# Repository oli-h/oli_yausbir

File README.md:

# oli_yausbir
A LIRC-Plugin (i.e. driver) for "yaUsbIR V3 LIRC USB IR Empfänger/Sender/Einschalter"

Just google for "yaUsbIR V3" and you quickly find info about this little InfraRed-Receiver/Transmitter/PowerSwitch-device

## Notes
- Work in progress
- Logging not yet proper. It just prints to stdout.

## Build and usage
Ensure you installed libusb-1.0-0-dev and liblirc-dev (`sudo apt install...`)

Build with `./build.sh` (requires cmake).

Then use the well-known LIRC-Tools like this:
- `mode2 -U build/ -H oli_yausbir`
- `xmode2 -U build/ -H oli_yausbir`
- `irrecord -U build/ -H oli_yausbir`
- `lircd --nodaemon -U build -H oli_yausbir`
- etc...

Finally copy the compile/link-result `liboli_yausbir.so` to directory `/usr/lib/x86_64-linux-gnu/lirc/plugins/` (Cross-check with property `plugindir` in *your* `/etc/lirc/lirc_options.conf`). Then you don't need to specify `-U ...` any more.

To avoid setting the driver explicit with `-H oli_yausbir` you can also set it globally in `/etc/lirc/lirc_options.conf`:

```
[lircd]
...
driver = oli_yausbir
...
```

## Sending control-commands
The yaUsbIr-Board understands several control-commands. This PlugIn-driver here supports sending such control-commands (Note: Sending 'any' IR-Codes with a real IR-Trasmitter-LED - which must be attached to the yaUsbIr-Board - is *not* yet supported)

You need to copy [yaUsbIR_V3_lircd.conf](./yaUsbIr-Doc/yausbirv3.003/yaUsbIR_V3_lircd.conf) to `/etc/lirc/lircd.conf.d/` and (re)start `lircd` first *before* you can can anything with `irsend`.

Check if "sending control-commands" work by switching the red LED (on yaUsbIr-Board) on and off:
- `irsend SEND_ONCE yaUsbIR_control C_IR 8 0 C_END` turn *off*
- `irsend SEND_ONCE yaUsbIR_control C_IR 8 1 C_END` turn *on*

The most relevant command for you then probably is:
- `irsend SEND_ONCE yaUsbIR_control C_IR 1 1 0 C_END` to start learning the "Power-IR-Code"

See [Anleitung_yaUsbIR V3.4.pdf](./yaUsbir-Doc/Anleitung_yaUsbIR V3.4.pdf) for details and a list of all commands.

## udev
Write this into `/lib/udev/rules.d/99-yausbir.rules` to give normal user access to the USB-Device.
Other wise you have to start all tools (`xmode2`, `irrecord`, etc) as root.

```
SUBSYSTEM=="usb", ATTRS{idVendor}=="10c4", ATTRS{idProduct}=="876c", MODE="0666"
```
Simply reboot to take effect

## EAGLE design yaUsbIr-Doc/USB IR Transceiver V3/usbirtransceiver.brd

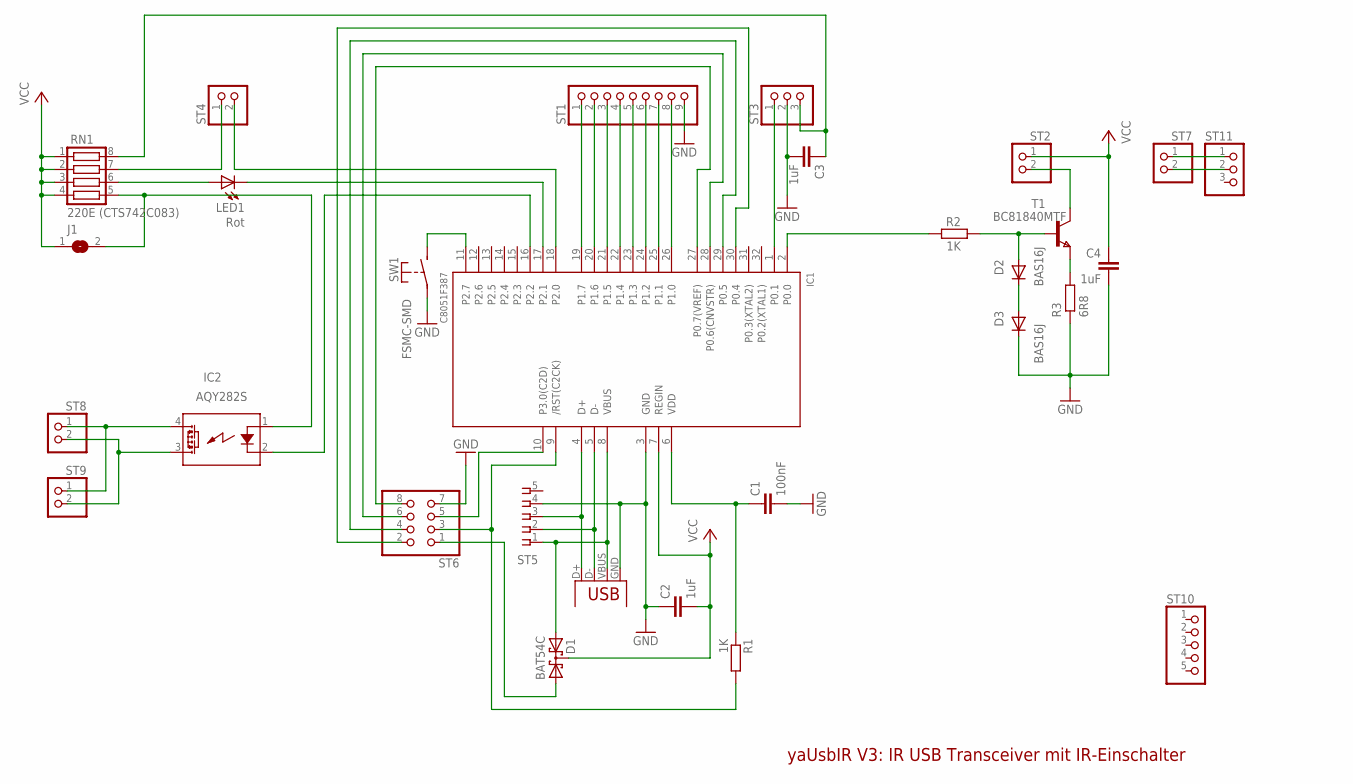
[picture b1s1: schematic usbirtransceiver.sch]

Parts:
C1: 100nF; C0805
C2, C3, C4: 1uF; C0805
D1: BAT54C; SOT23
D2, D3: BAS16J; SOD323-R
IC1: C8051F387; TQFP32-08
IC2: AQY282S; SOP04
J1: SJ
LED1: Rot; CHIP-LED0805
R1, R2: 1K; R0805
R3: 6R8; M1206
RN1: 220E (CTS742C083); CTS742C083
ST1: PINHD-1X9; 1X09
ST2, ST4, ST7, ST8, ST9: PINHD-1X2; 1X02
ST3, ST11: PINHD-1X3; 1X03
ST5: CON5PINSMD2.54; SMDTOP5
ST6: PINHD-2X4; 2X04
ST10: PINHD-1X5_2.54-SMD-90°; 1X05SMD/90
ST12: USB-MB-S
SW1: FSMC-SMD
T1: BC81840MTF; SOT-23

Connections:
GND: C1.2, C2.1, C3.2, C4.2, D3.C, IC1.3 (GND), R3.1, ST1.9, ST3.2, ST5.4, ST6.7, ST12.GND, SW1.P$1
unnamed: LED1.A, RN1.6
unnamed: RN1.7, ST4.1
unnamed: IC2.1 (A), J1.2, RN1.5
unnamed: IC1.19 (P1.7), ST1.1
unnamed: IC1.20 (P1.6), ST1.2
unnamed: IC1.21 (P1.5), ST1.3
unnamed: IC1.22 (P1.4), ST1.4
unnamed: IC1.23 (P1.3), ST1.5
unnamed: ST2.2, T1.1 (C)
unnamed: IC1.24 (P1.2), ST1.6
unnamed: IC1.25 (P1.1), ST1.7
unnamed: IC1.26 (P1.0), ST1.8
unnamed: IC1.17 (P2.1), LED1.C
unnamed: IC2.4 (DS1), ST8.1, ST9.1
unnamed: C1.1, IC1.6 (VDD), R1.1
unnamed: ST7.1, ST11.1
unnamed: IC1.27 (P0.7(VREF)), ST6.8
unnamed: D2.C, D3.A
unnamed: IC1.18 (P2.0), ST4.2
unnamed: IC1.16 (P2.2), IC2.2 (K)
unnamed: D2.A, R2.1, T1.3 (B)
unnamed: IC1.5 (D-), ST5.2, ST12.D-
unnamed: IC1.28 (P0.6(CNVSTR)), ST6.6
unnamed: R3.2, T1.2 (E)
unnamed: IC1.4 (D+), ST5.3, ST12.D+
unnamed: IC2.3 (DS2), ST8.2, ST9.2
unnamed: IC1.30 (P0.4), ST6.2
unnamed: IC1.10 (P3.0(C2D)), ST6.5
unnamed: IC1.1 (P0.1), ST3.1
unnamed: IC1.29 (P0.5), ST6.4
unnamed: IC1.9 (/RST(C2CK)), R1.2, ST6.3
unnamed: ST7.2, ST11.2
unnamed: IC1.11 (P2.7), SW1.P$2 (S)
unnamed: IC1.2 (P0.0), R2.2
unnamed: C3.1, RN1.8, ST3.3
VCC: C2.2, C4.1, D1.3 (CC), IC1.7 (REGIN), J1.1, RN1.1, RN1.2, RN1.3, RN1.4, ST2.1
VCC1: D1.2 (A2), IC1.8 (VBUS), ST5.1, ST12.VBUS
VCC2: D1.1 (A1), ST6.1

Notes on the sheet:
yaUsbIR V3: IR USB Transceiver mit IR-Einschalter

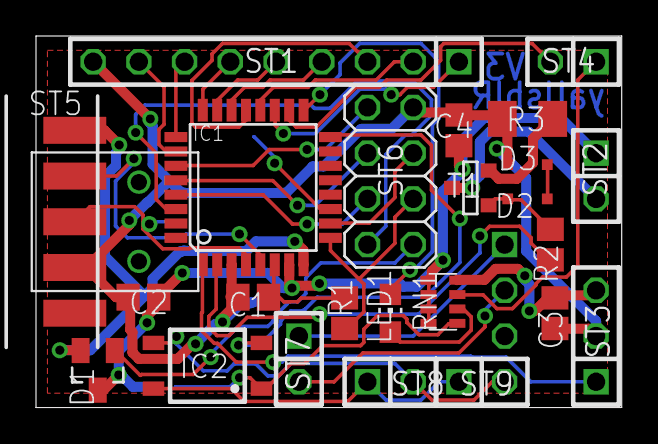
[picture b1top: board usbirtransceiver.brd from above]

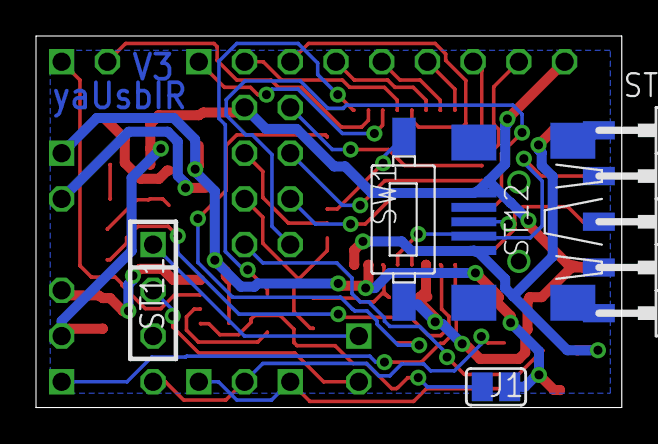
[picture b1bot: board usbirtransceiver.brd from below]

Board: 2 copper layers, 32.5 x 20.6 mm, 29 parts (5 on the bottom side), 39 nets.

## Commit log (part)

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2020-10-25 Source for yaUsbIr-Device
    - Source-Code for the (embedded) controller
    - PCB-Layout
    - PDF-Description
    Grabbed from:
    https://www.vdr-portal.de/forum/index.php?thread/116157-yausbir-v3-lirc-usb-ir-empf%C3%A4nger-sender-einschalter/&postID=1282868#post1282868
2020-10-25 access yaUsbIr
2020-10-27 first really working implemention. Works with xmode2, mode2, irrecord and lircd like a charm
2020-11-07 Support for sending yaUsbIr-commands
2020-11-08 Release-Config
2020-11-10 Provide a precompiled library (for the impatient)
